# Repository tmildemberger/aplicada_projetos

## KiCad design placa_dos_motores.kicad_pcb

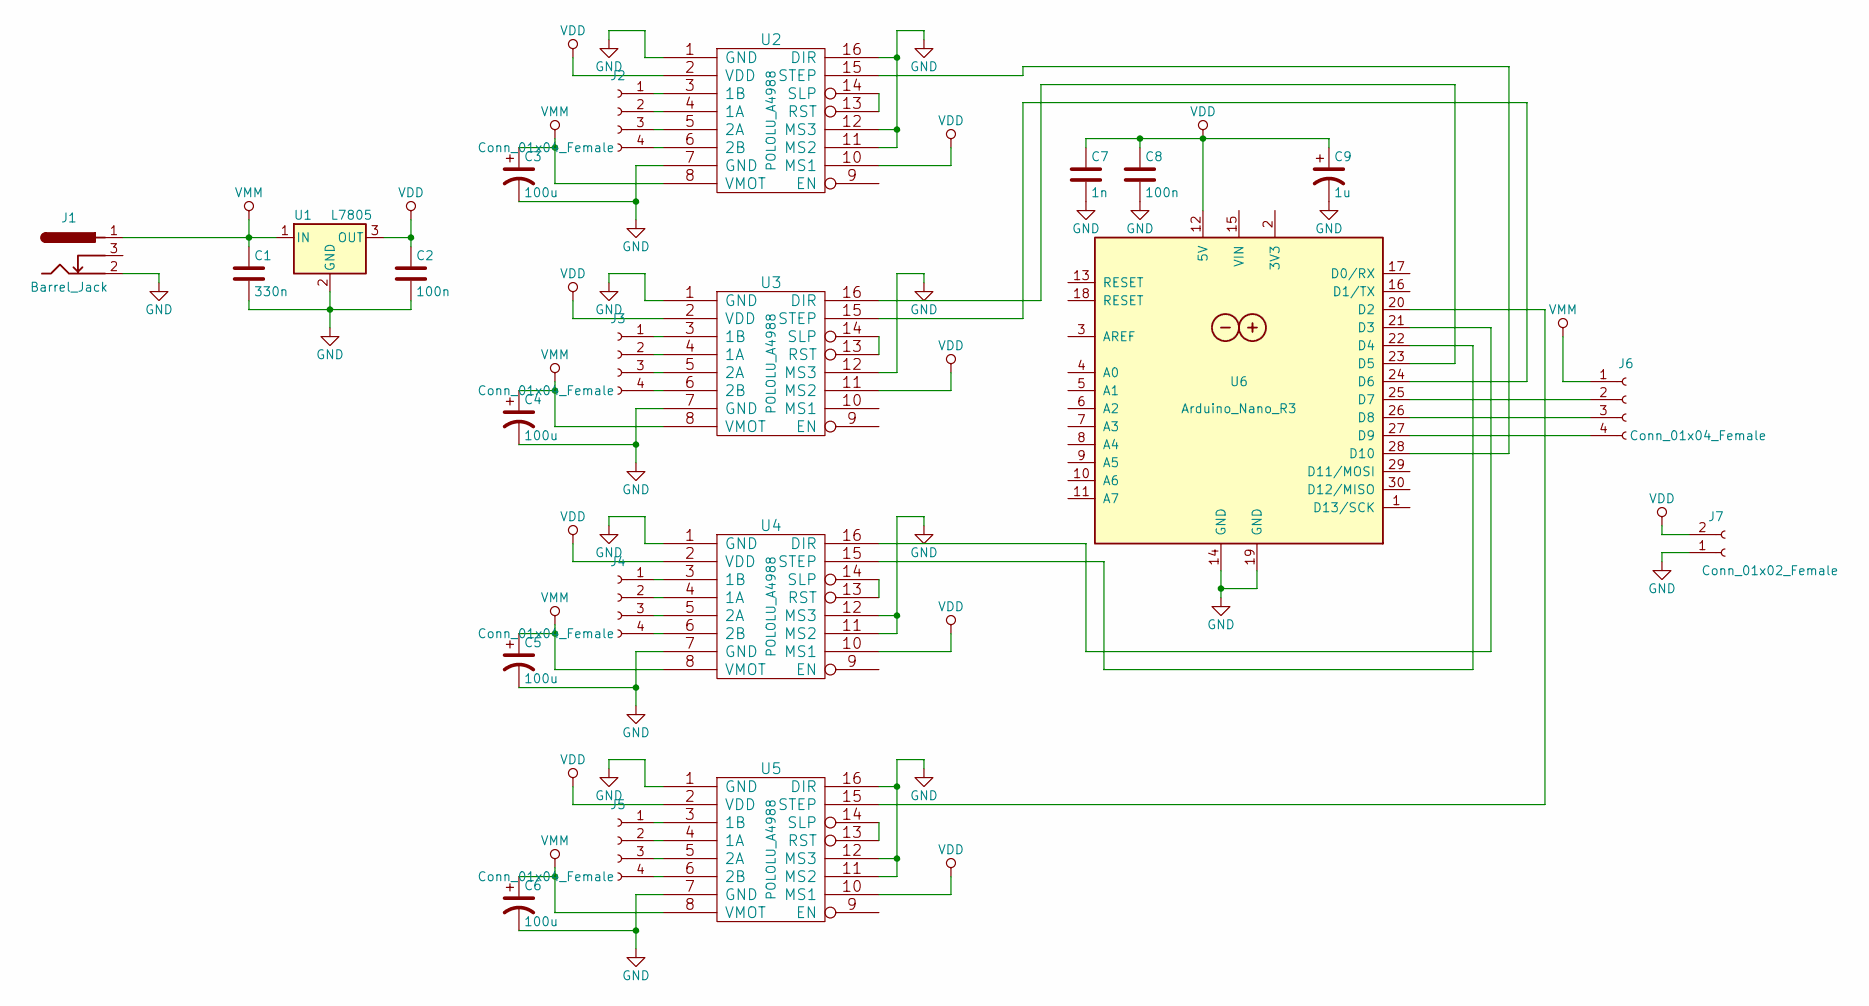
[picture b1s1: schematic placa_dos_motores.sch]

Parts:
C1: 330n; C_Rect_L7.0mm_W2.5mm_P5.00mm
C2, C8: 100n; C_Rect_L7.0mm_W2.5mm_P5.00mm
C3, C4, C5, C6: 100u; CP_Radial_D6.3mm_P2.50mm
C7: 1n; C_Rect_L7.0mm_W2.5mm_P5.00mm
C9: 1u; CP_Radial_D6.3mm_P2.50mm
J1: Barrel_Jack; BARREL_JACK
J2, J3, J4, J5, J6: Conn_01x04_Female; TerminalBlock_bornier-4_P5.08mm
J7: Conn_01x02_Female; TerminalBlock_bornier-2_P5.08mm
U1: L7805; TO-220-3_Vertical
U2, U3, U4, U5: POLOLU_A4988; Pololu_Breakout-16_15.2x20.3mm
U6: Arduino_Nano_R3; Arduino_Nano

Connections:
GND: C1.2, C2.2, C3.2, C4.2, C5.2, C6.2, C7.2, C8.2, C9.2, J1.2, J7.1, U1.2 (GND), U2.1 (GND), U2.7 (GND), U2.11 (MS2), U2.12 (MS3), U2.16 (DIR), U3.1 (GND), U3.7 (GND), U3.12 (MS3), U4.1 (GND), U4.7 (GND), U4.11 (MS2), U4.12 (MS3), U5.1 (GND), U5.7 (GND), U5.11 (MS2), U5.12 (MS3), U5.16 (DIR), U6.14 (GND), U6.19 (GND)
unnamed: J2.1, U2.3 (1B)
unnamed: J2.2, U2.4 (1A)
unnamed: J2.3, U2.5 (2A)
unnamed: J2.4, U2.6 (2B)
unnamed: J3.1, U3.3 (1B)
unnamed: J3.2, U3.4 (1A)
unnamed: J3.3, U3.5 (2A)
unnamed: J3.4, U3.6 (2B)
unnamed: J4.1, U4.3 (1B)
unnamed: J4.2, U4.4 (1A)
unnamed: J4.3, U4.5 (2A)
unnamed: J4.4, U4.6 (2B)
unnamed: J5.1, U5.3 (1B)
unnamed: J5.2, U5.4 (1A)
unnamed: J5.3, U5.5 (2A)
unnamed: J5.4, U5.6 (2B)
unnamed: J6.2, U6.25 (D7)
unnamed: J6.3, U6.26 (D8)
unnamed: J6.4, U6.27 (D9)
unnamed: U2.13 (RST), U2.14 (SLP)
unnamed: U2.15 (STEP), U6.28 (D10)
unnamed: U3.13 (RST), U3.14 (SLP)
unnamed: U3.15 (STEP), U6.24 (D6)
unnamed: U3.16 (DIR), U6.23 (D5)
unnamed: U4.13 (RST), U4.14 (SLP)
unnamed: U4.15 (STEP), U6.22 (D4)
unnamed: U4.16 (DIR), U6.21 (D3)
unnamed: U5.13 (RST), U5.14 (SLP)
unnamed: U5.15 (STEP), U6.20 (D2)
VDD: C2.1, C7.1, C8.1, C9.1, J7.2, U1.3 (OUT), U2.2 (VDD), U2.10 (MS1), U3.2 (VDD), U3.11 (MS2), U4.2 (VDD), U4.10 (MS1), U5.2 (VDD), U5.10 (MS1), U6.12 (5V)
VMM: C1.1, C3.1, C4.1, C5.1, C6.1, J1.1, J6.1, U1.1 (IN), U2.8 (VMOT), U3.8 (VMOT), U4.8 (VMOT), U5.8 (VMOT)

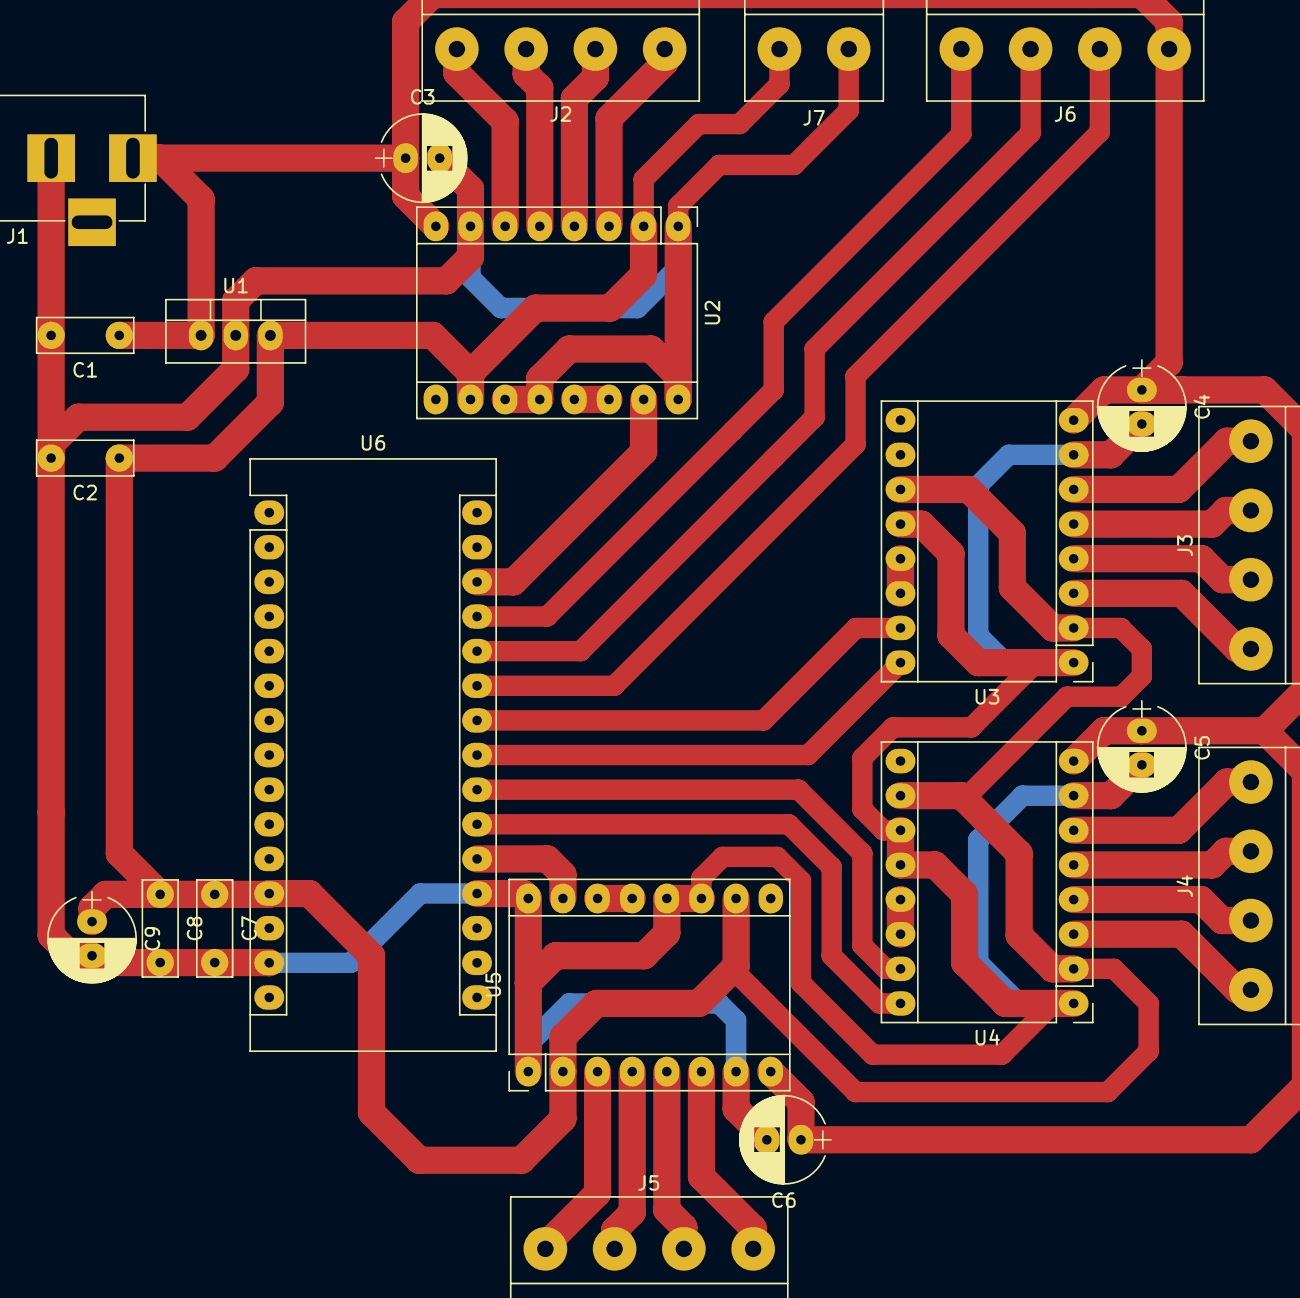
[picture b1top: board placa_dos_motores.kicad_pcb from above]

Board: 2 copper layers, 22 parts (0 on the bottom side), 32 nets.

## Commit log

2018-12-05 guardar
2018-12-14 estado atual e final
2018-12-14 placas
